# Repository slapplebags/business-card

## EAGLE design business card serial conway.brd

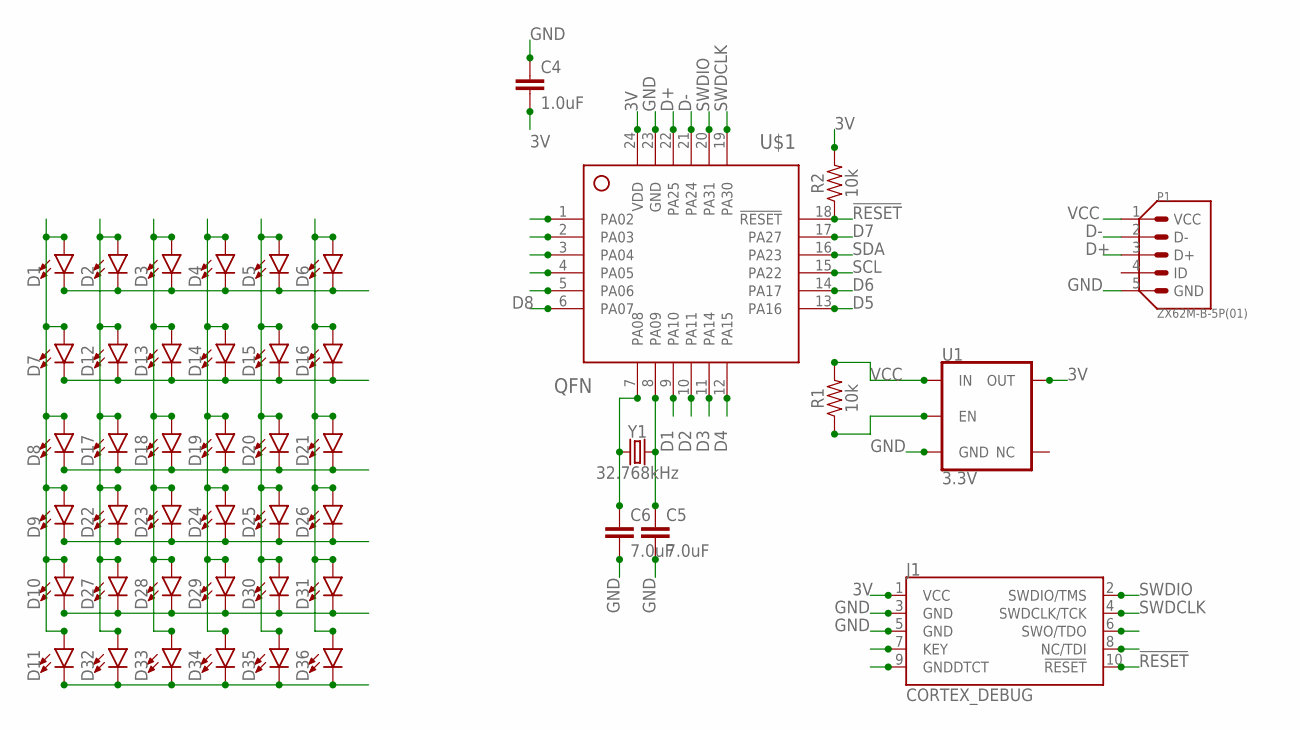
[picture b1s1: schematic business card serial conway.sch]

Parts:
C4: 1.0uF; 0402
C5, C6: 7.0uF; 0402
D1, D2, D3, D4, D5, D6, D7, D8, D9, D10, D11, D12, D13, D14, D15, D16, D17, D18, D19, D20, D21, D22, D23, D24, D25, D26, D27, D28, D29, D30, D31, D32, D33, D34, D35, D36: LED0603; LED-0603
J1: CORTEX_DEBUG; 2X5-PTH-1.27MM
P1: ZX62M-B-5P(01); HRS_ZX62M-B-5P(01)
R1, R2: 10k; 0603
U1: 3.3V; SOT23-5
U$1: QFN; QFN24-4X4
Y1: 32.768kHz; CRYSTAL-SMD-3.2X1.5MM

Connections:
3V: C4.2, J1.1 (VCC), R2.2, U1.5 (OUT), U$1.24 (VDD)
!RESET: J1.10 (!RESET), R2.1, U$1.18 (!RESET)
D1: U$1.9 (PA10)
D2: U$1.10 (PA11)
D3: U$1.11 (PA14)
D4: U$1.12 (PA15)
D5: U$1.13 (PA16)
D6: U$1.14 (PA17)
D7: U$1.17 (PA27)
D8: U$1.6 (PA07)
D+: P1.3 (D+), U$1.22 (PA25)
D-: P1.2 (D-), U$1.21 (PA24)
GND: C4.1, C5.2, C6.2, J1.3 (GND), J1.5 (GND), P1.5 (GND), U1.2 (GND), U$1.23 (GND)
unnamed: D1.C, D2.C, D3.C, D4.C, D5.C, D6.C
unnamed: C6.1, U$1.7 (PA08), Y1.P$1 (1)
unnamed: C5.1, U$1.8 (PA09), Y1.P$2 (2)
unnamed: R1.1, U1.3 (EN)
unnamed: D7.C, D12.C, D13.C, D14.C, D15.C, D16.C
unnamed: D8.C, D17.C, D18.C, D19.C, D20.C, D21.C
unnamed: D9.C, D22.C, D23.C, D24.C, D25.C, D26.C
unnamed: D10.C, D27.C, D28.C, D29.C, D30.C, D31.C
unnamed: D11.C, D32.C, D33.C, D34.C, D35.C, D36.C
unnamed: D1.A, D7.A, D8.A, D9.A, D10.A, D11.A
unnamed: D2.A, D12.A, D17.A, D22.A, D27.A, D32.A
unnamed: D3.A, D13.A, D18.A, D23.A, D28.A, D33.A
unnamed: D4.A, D14.A, D19.A, D24.A, D29.A, D34.A
unnamed: D5.A, D15.A, D20.A, D25.A, D30.A, D35.A
unnamed: D6.A, D16.A, D21.A, D26.A, D31.A, D36.A
SCL: U$1.15 (PA22)
SDA: U$1.16 (PA23)
SWDCLK: J1.4 (SWDCLK/TCK), U$1.19 (PA30)
SWDIO: J1.2 (SWDIO/TMS), U$1.20 (PA31)
VCC: P1.1 (VCC), R1.2, U1.1 (IN)

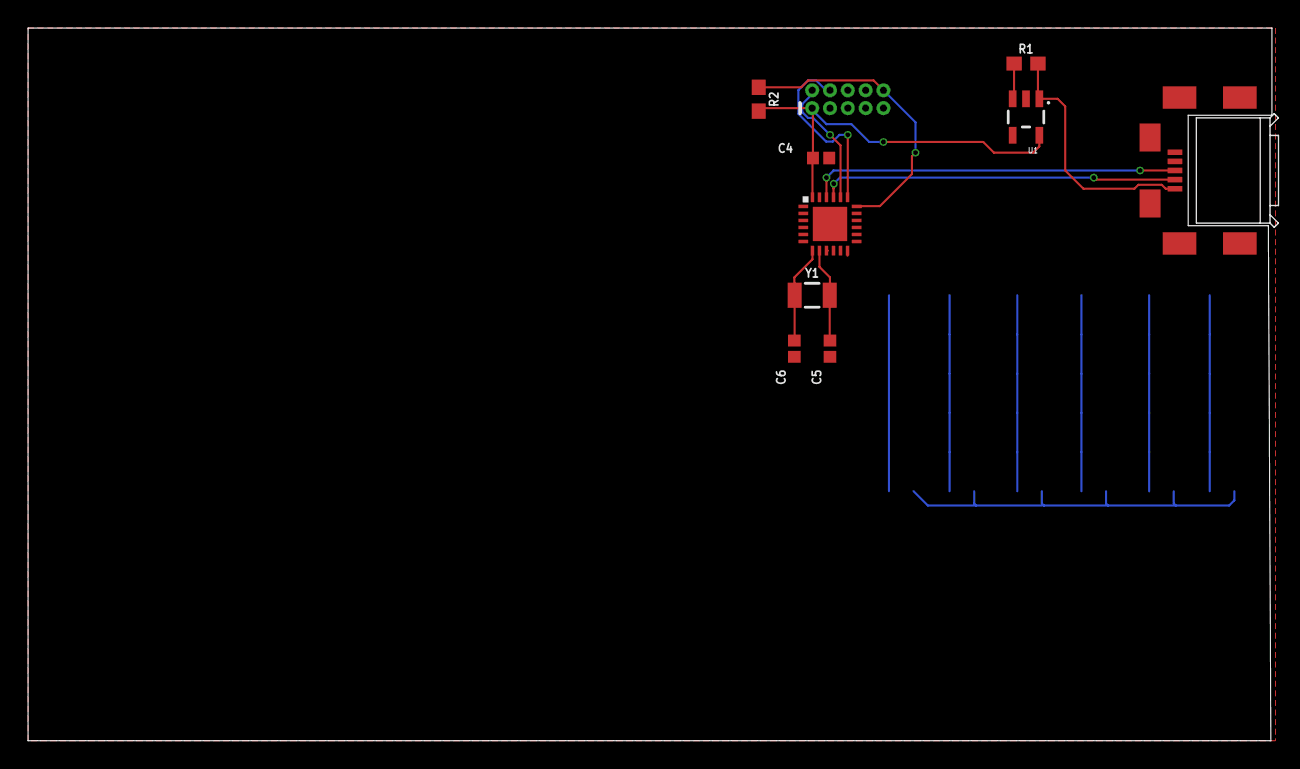
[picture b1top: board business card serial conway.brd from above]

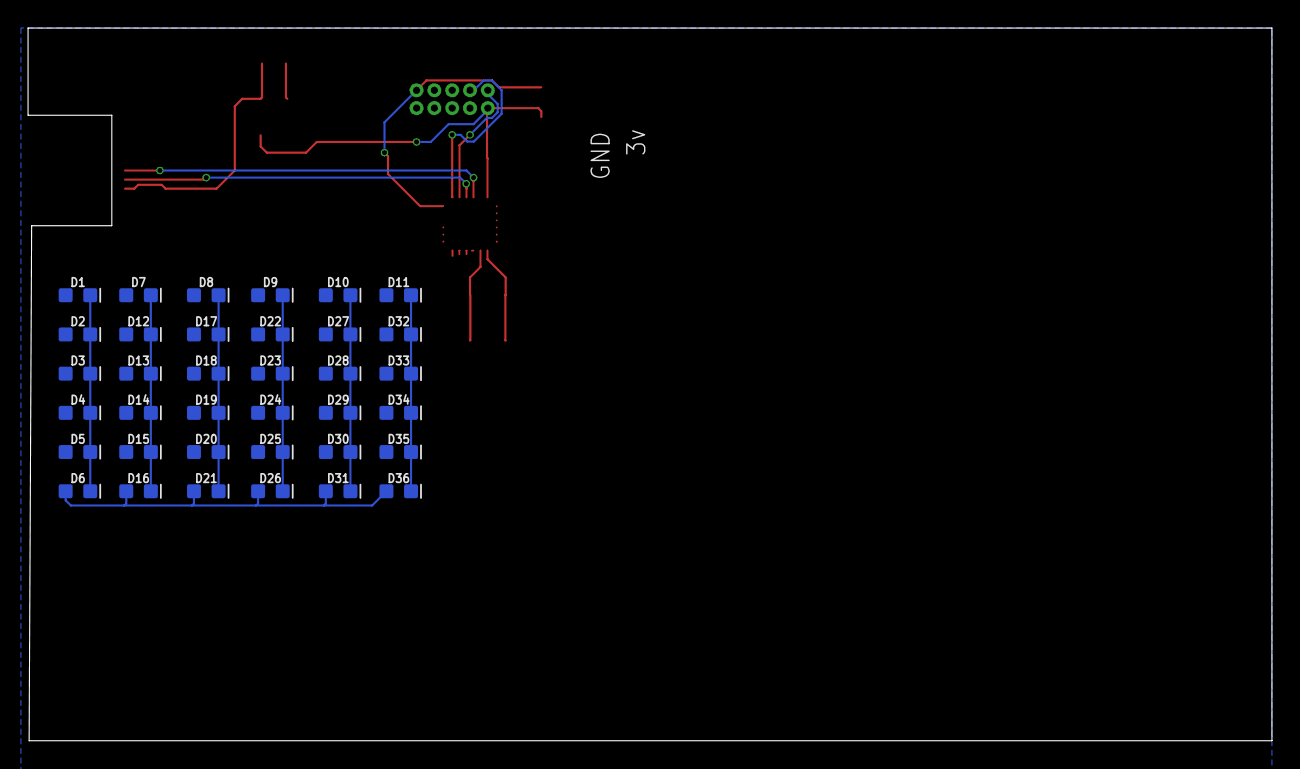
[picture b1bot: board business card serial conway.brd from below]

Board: 2 copper layers, 88.6 x 50.8 mm, 46 parts (36 on the bottom side), 23 nets.

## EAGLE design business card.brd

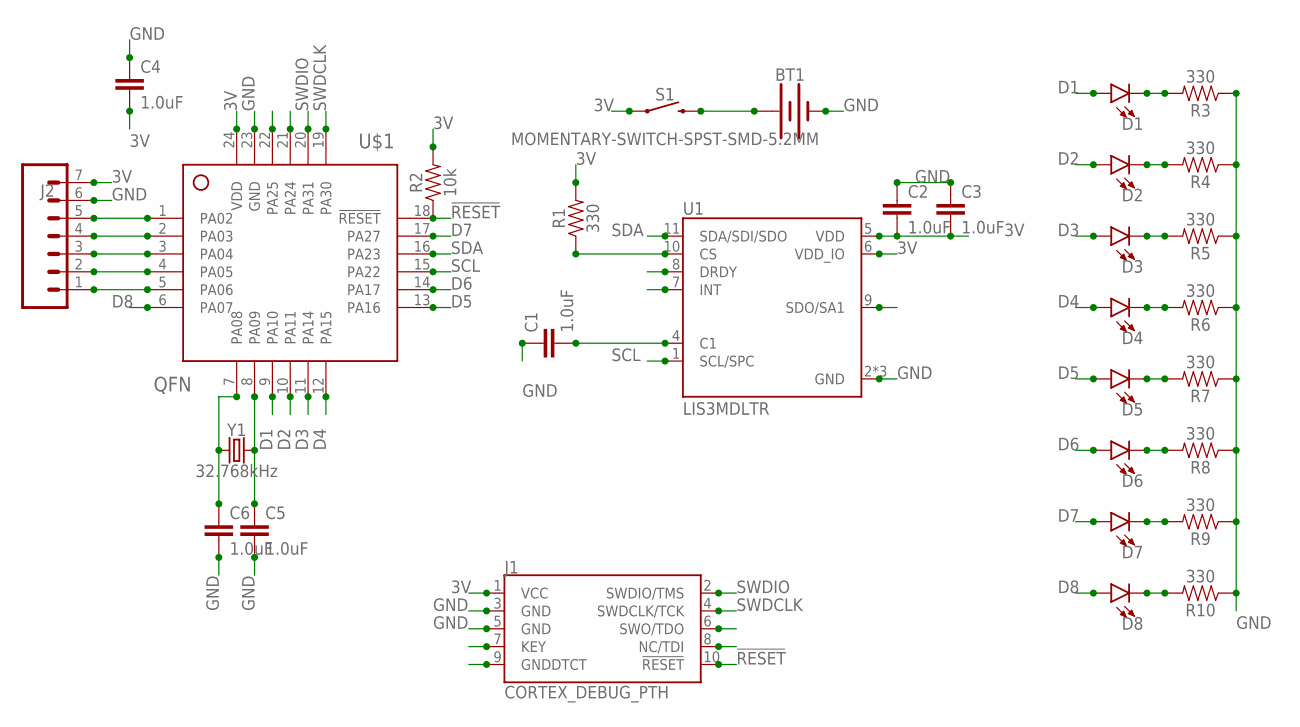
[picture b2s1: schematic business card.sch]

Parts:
BT1: BATTERY-20MM_SMD_4LEGS; BATTCON_20MM_4LEGS
C1, C2, C3, C4, C5, C6: 1.0uF; 0402
D1, D2, D3, D4, D5, D6, D7, D8: LED0603; LED-0603
J1: CORTEX_DEBUG_PTH; 2X5-PTH-1.27MM
J2: CONN_07; 1X07
R1, R3, R4, R5, R6, R7, R8, R9, R10: 330; 0603
R2: 10k; 0603
S1: MOMENTARY-SWITCH-SPST-SMD-5.2MM; TACTILE_SWITCH_SMD_5.2MM
U1: LIS3MDLTR; LGA12R50P4X4_200X200X100
U$1: QFN; QFN24-4X4
Y1: 32.768kHz; CRYSTAL-SMD-3.2X1.5MM

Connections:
3V: C2.2, C3.2, C4.2, J1.1 (VCC), J2.7, R1.2, R2.2, S1.1, U1.5 (VDD), U1.6 (VDD_IO), U$1.24 (VDD)
!RESET: J1.10 (!RESET), R2.1, U$1.18 (!RESET)
D1: D1.A, U$1.9 (PA10)
D2: D2.A, U$1.10 (PA11)
D3: D3.A, U$1.11 (PA14)
D4: D4.A, U$1.12 (PA15)
D5: D5.A, U$1.13 (PA16)
D6: D6.A, U$1.14 (PA17)
D7: D7.A, U$1.17 (PA27)
D8: D8.A, U$1.6 (PA07)
GND: BT1.NEGATIVE (-), C1.1, C2.1, C3.1, C4.1, C5.2, C6.2, J1.3 (GND), J1.5 (GND), J2.6, R3.1, R4.1, R5.1, R6.1, R7.1, R8.1, R9.1, R10.1, U1.2 (GND), U1.3 (GND), U1.12 (GND), U$1.23 (GND)
unnamed: D1.C, R3.2
unnamed: C6.1, U$1.7 (PA08), Y1.P$1 (1)
unnamed: C5.1, U$1.8 (PA09), Y1.P$2 (2)
unnamed: BT1.POSITIVE@1 (+), BT1.POSITIVE@2 (+), BT1.POSITIVE@3 (+), BT1.POSITIVE@4 (+), S1.3 (2)
unnamed: C1.2, U1.4 (C1)
unnamed: R1.1, U1.10 (CS)
unnamed: J2.5, U$1.1 (PA02)
unnamed: J2.4, U$1.2 (PA03)
unnamed: J2.3, U$1.3 (PA04)
unnamed: J2.2, U$1.4 (PA05)
unnamed: J2.1, U$1.5 (PA06)
unnamed: D2.C, R4.2
unnamed: D3.C, R5.2
unnamed: D4.C, R6.2
unnamed: D5.C, R7.2
unnamed: D6.C, R8.2
unnamed: D7.C, R9.2
unnamed: D8.C, R10.2
SCL: U1.1 (SCL/SPC), U$1.15 (PA22)
SDA: U1.11 (SDA/SDI/SDO), U$1.16 (PA23)
SWDCLK: J1.4 (SWDCLK/TCK), U$1.19 (PA30)
SWDIO: J1.2 (SWDIO/TMS), U$1.20 (PA31)

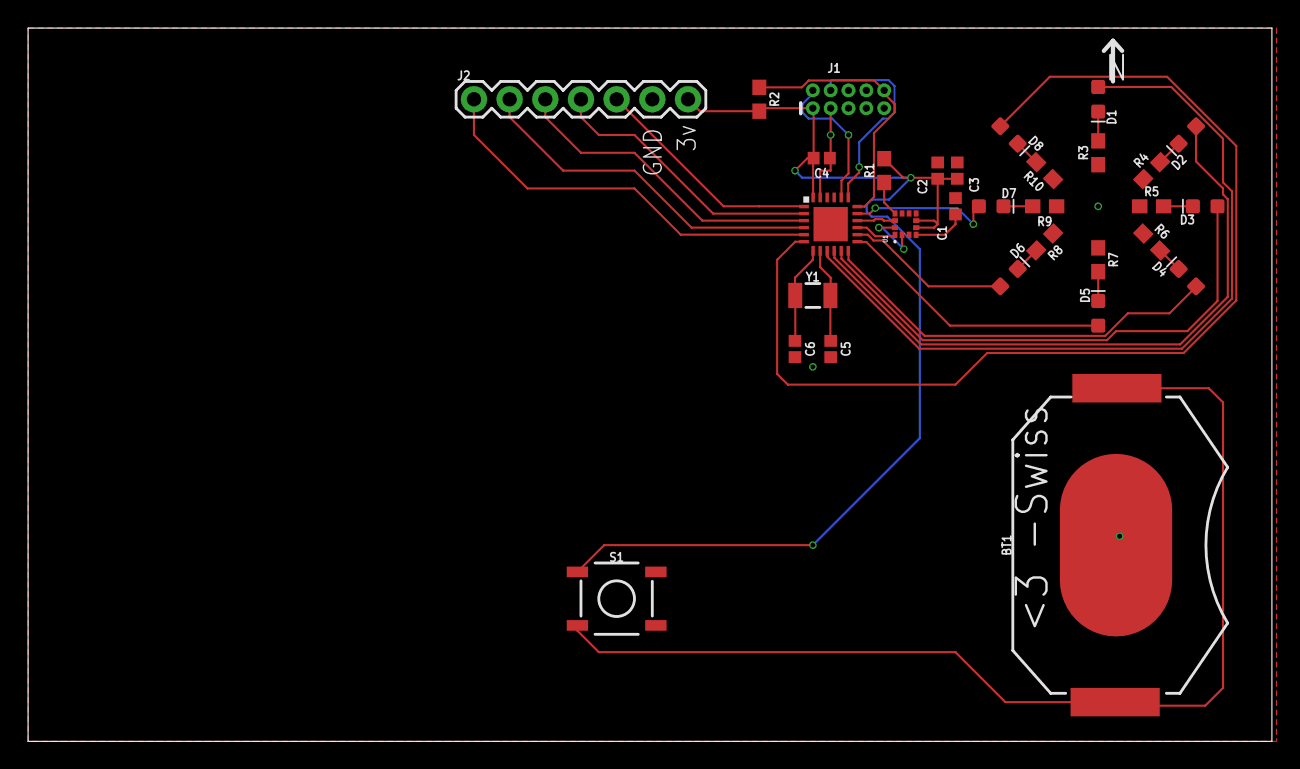
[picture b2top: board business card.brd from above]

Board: 2 copper layers, 88.6 x 50.8 mm, 31 parts (0 on the bottom side), 33 nets.

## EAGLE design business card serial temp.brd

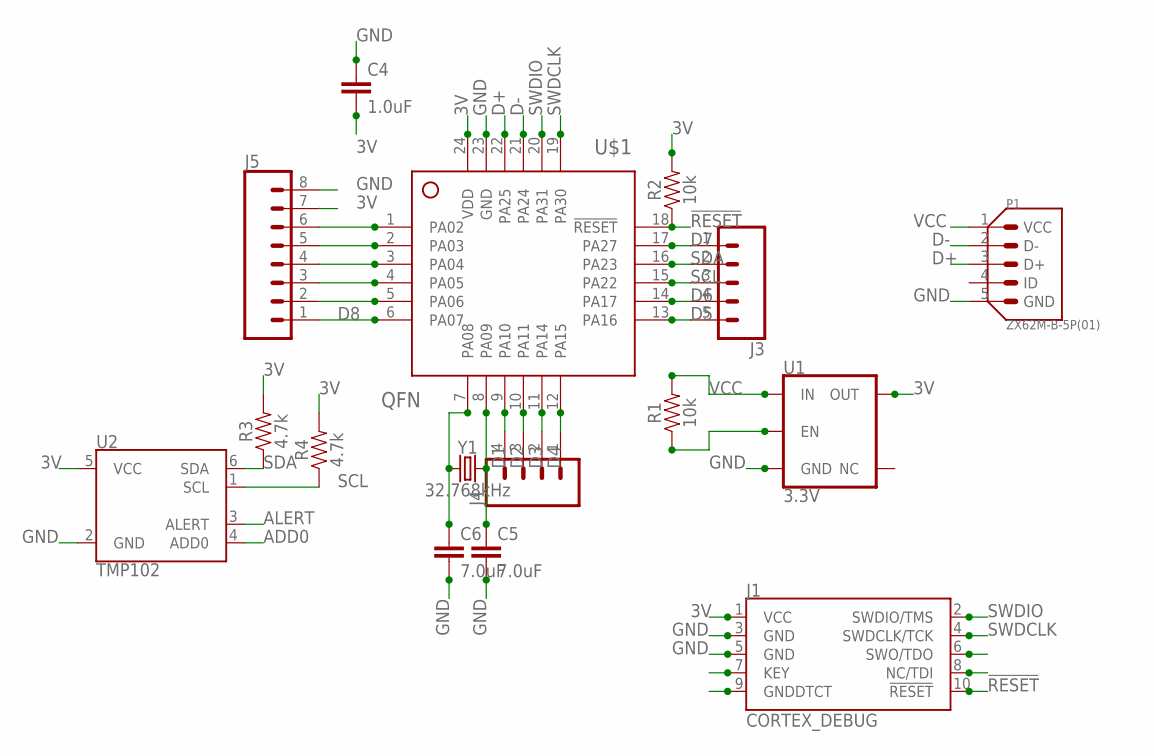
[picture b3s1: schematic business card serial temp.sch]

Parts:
C4: 1.0uF; 0402
C5, C6: 7.0uF; 0402
J1: CORTEX_DEBUG; 2X5-PTH-1.27MM
J3: CONN_05; 1X05
J4: CONN_04; 1X04
J5: CONN_08"; 1X08
P1: ZX62M-B-5P(01); HRS_ZX62M-B-5P(01)
R1, R2: 10k; 0603
R3, R4: 4.7k; 0603
U1: 3.3V; SOT23-5
U2: TMP102; SOT563
U$1: QFN; QFN24-4X4
Y1: 32.768kHz; CRYSTAL-SMD-3.2X1.5MM

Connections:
3V: C4.2, J1.1 (VCC), J5.7, R2.2, R3.2, R4.2, U1.5 (OUT), U2.5 (VCC), U$1.24 (VDD)
!RESET: J1.10 (!RESET), R2.1, U$1.18 (!RESET)
ADD0: U2.4 (ADD0)
ALERT: U2.3 (ALERT)
D1: J4.4, U$1.9 (PA10)
D2: J4.3, U$1.10 (PA11)
D3: J4.2, U$1.11 (PA14)
D4: J4.1, U$1.12 (PA15)
D5: J3.5, U$1.13 (PA16)
D6: J3.4, U$1.14 (PA17)
D7: J3.1, U$1.17 (PA27)
D8: J5.1, U$1.6 (PA07)
D+: P1.3 (D+), U$1.22 (PA25)
D-: P1.2 (D-), U$1.21 (PA24)
GND: C4.1, C5.2, C6.2, J1.3 (GND), J1.5 (GND), J5.8, P1.5 (GND), U1.2 (GND), U2.2 (GND), U$1.23 (GND)
unnamed: C6.1, U$1.7 (PA08), Y1.P$1 (1)
unnamed: C5.1, U$1.8 (PA09), Y1.P$2 (2)
unnamed: R1.1, U1.3 (EN)
unnamed: J5.6, U$1.1 (PA02)
unnamed: J5.5, U$1.2 (PA03)
unnamed: J5.4, U$1.3 (PA04)
unnamed: J5.3, U$1.4 (PA05)
unnamed: J5.2, U$1.5 (PA06)
SCL: J3.3, R4.1, U2.1 (SCL), U$1.15 (PA22)
SDA: J3.2, R3.1, U2.6 (SDA), U$1.16 (PA23)
SWDCLK: J1.4 (SWDCLK/TCK), U$1.19 (PA30)
SWDIO: J1.2 (SWDIO/TMS), U$1.20 (PA31)
VCC: P1.1 (VCC), R1.2, U1.1 (IN)

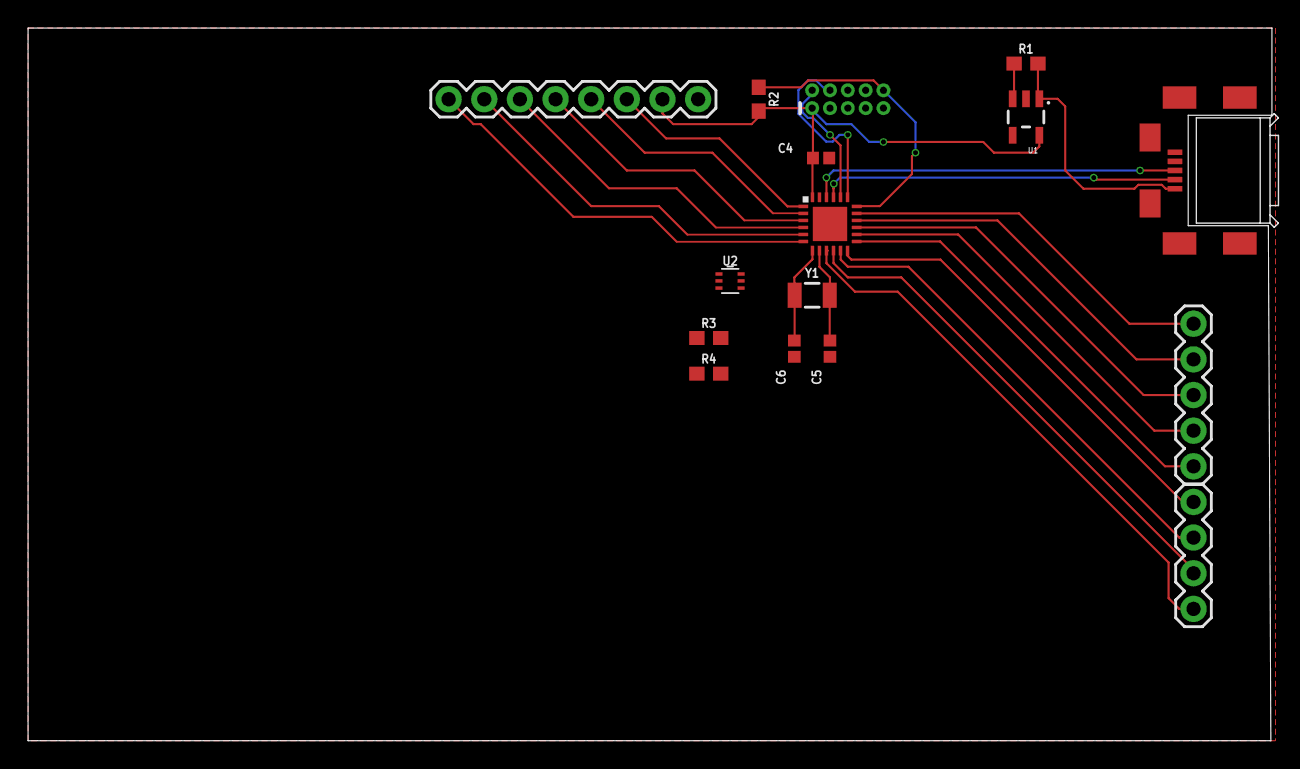
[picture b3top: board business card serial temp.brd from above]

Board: 2 copper layers, 88.6 x 50.8 mm, 16 parts (0 on the bottom side), 26 nets.

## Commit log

2019-02-22 Create License

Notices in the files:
parts and their libraries:
SparkFun-Connectors: Licensing: Creative Commons ShareAlike 4.0 International - https://creativecommons.org/licenses/by-sa/4.0
